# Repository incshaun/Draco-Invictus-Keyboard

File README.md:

# Draco-Invictus-Keyboard
Converts wired keyboards into bluetooth keyboards

This project contains the software and hardware schematics for a device that allows older PS/2 style keyboards to appear as a bluetooth keyboard. The board uses an ESP32 system-on-chip microcontroller to provide the processing and bluetooth functionality, and requires some level converters to manage the 3.3V required by the ESP32 and 5V required by the PS/2 keyboard.

The software is largely derived from:
* https://github.com/T-vK/ESP32-BLE-Keyboard: for the bluetooth functionality.
* https://github.com/techpaul/PS2KeyAdvanced: for the PS/2 keyboard handling.
* https://github.com/ab0tj/PS2KeyAdvanced-Pico: for some fixes to PS/2 keyboard handling using ESP32
The licenses from these repositories applies to the corresponding code in this repository.

# Software

The software can be compiled and installed using the arduino IDE configured to support an ESP32 Dev Module.

The current version handles the standard keys, as well as capslock and numlock. Additional multimedia keys are not currently supported.

# Hardware

Notes:
* Power to the unit is supplied using an USB connector. A powerbank is a suitable power source, and allows the keyboard to be portable.
* The ESP32 module is attached to an adapter board (e.g., https://www.komputer.de/zen/index.php?main_page=product_info&products_id=422). This provides buttons to reset and flash the software onto the chip. Note that pull-up resistors on the EN and IO0 lines are required and may not be present on the adapter board. Replacements ($10 \mathsf{k\Omega}$) are included in the schematic and board layout.
* External connector J1 is provided to attached an FTDI FT232RL USB Serial Converter module (e.g., https://littlebirdelectronics.com.au/products/ftdi-ft232rl-usb-to-ttl-serial-converter-adapter-module-5v-and-3-3v). Make sure that this is connected the right way around (GND pin should connect to the ground line), and that the voltage level is set to 3.3 V using the jumper on the board. This module can be removed once the software has been transferred.

The circuit diagram schematic:

The circuit board layout:

## Views of an assembled board

Top:

Bottom (flipped to correspond with circuit layout):

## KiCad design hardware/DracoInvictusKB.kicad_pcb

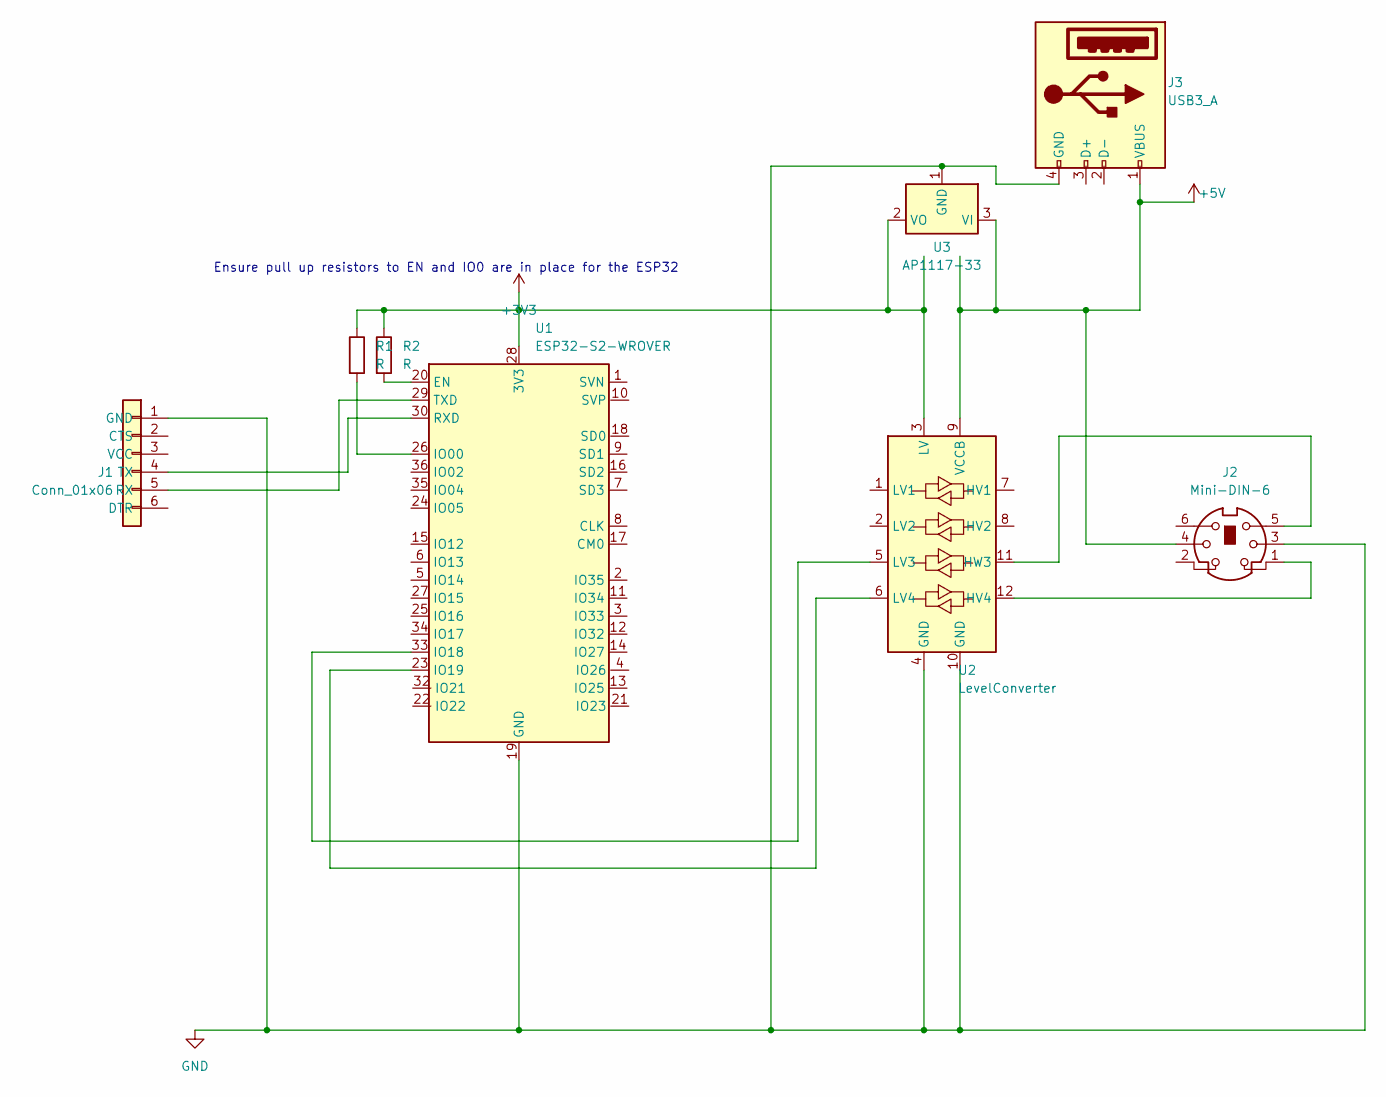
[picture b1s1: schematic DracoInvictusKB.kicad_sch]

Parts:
J1: Conn_01x06; PinHeader_1x06_P2.54mm_Vertical
J2: Mini-DIN-6; Connector_Mini-DIN_Female_6Pin_2rows
J3: USB3_A; PinHeader_1x02_P2.54mm_Vertical
R1, R2: R; R_Box_L8.4mm_W2.5mm_P5.08mm
U1: ESP32-S2-WROVER
U2: LevelConverter
U3: AP1117-33; SOT-223-3_TabPin2

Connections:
+3V3: R1.1, R2.1, U1.28 (3V3), U2.3 (LV), U3.2 (VO)
+5V: J2.4, J3.1 (VBUS), U2.9 (VCCB), U3.3 (VI)
GND: J1.1 (GND), J2.3, J3.4 (GND), U1.19 (GND), U1.31 (GND), U2.4 (GND), U2.10 (GND), U3.1 (GND)
unnamed: J1.5 (RX), U1.29 (TXD)
unnamed: J1.4 (TX), U1.30 (RXD)
unnamed: R2.2, U1.20 (EN)
unnamed: R1.2, U1.26 (IO00)
unnamed: U1.33 (IO18), U2.5 (LV3)
unnamed: U1.23 (IO19), U2.6 (LV4)
unnamed: J2.1, U2.12 (HV4)
unnamed: J2.5, U2.11 (HW3)

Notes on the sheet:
Ensure pull up resistors to EN and IO0 are in place for the ESP32

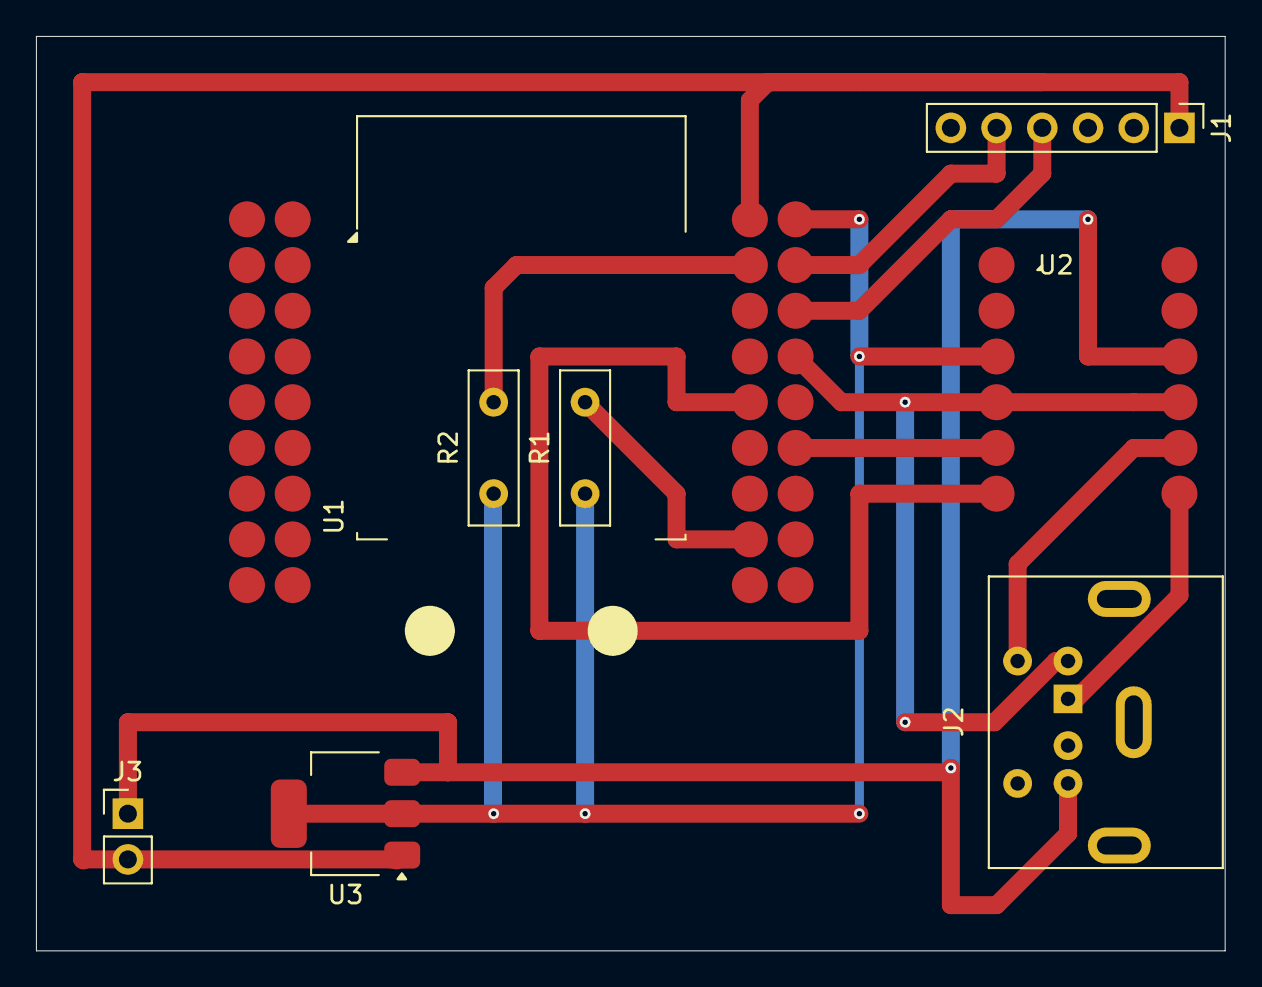
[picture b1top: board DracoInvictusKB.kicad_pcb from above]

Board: 2 copper layers, 66.0 x 50.8 mm, 8 parts (0 on the bottom side), 11 nets.

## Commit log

2025-03-08 Added in the kicad files for the circuit board
2025-03-08 Added software to translate ps/2 keystroke to bluetooth keystrokes
2025-03-08 Included some images showing the physical board
2025-03-08 Update README.md with project details and notes
